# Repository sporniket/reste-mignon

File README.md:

# Sporniket's 'ReSTe mignon'

> [WARNING] Please read carefully this note before using this project. It contains important facts.

Content

1. What is **Sporniket's 'ReSTe mignon'**, and when to use it ?
2. What should you know before using **Sporniket's 'ReSTe mignon'** ?
3. How to use **Sporniket's 'ReSTe mignon'** ?
4. Known issues
5. Miscellanous

## 1. What is **Sporniket's 'ReSTe mignon'**, and when to use it ?

**Sporniket's 'ReSTe mignon'** is a _RE_-make of the computer known as 'Atari _STe_', on a B5-sized (250×175 mm) PCB. Smaller, so 'cute', hence '_mignon_'.

This is a project made with [Kicad](https://www.kicad.org/). I started this work [from the conversion of the original Atari STe schematics](https://github.com/sporniket/kicad-conversions--atari-ste-motherboard--c300780-001).

### Licence

**Sporniket's 'ReSTe mignon'** is marked with CC0 1.0 Universal. To view a copy of this license, visit http://creativecommons.org/publicdomain/zero/1.0

**Sporniket's 'ReSTe mignon'** is distributed in the hope that it will be useful, but WITHOUT ANY WARRANTY; without even the implied warranty of MERCHANTABILITY or FITNESS FOR A PARTICULAR PURPOSE.

### Releases notes

#### extension-cpu-68k-plcc68--v1.0.0-beta.1

First beta implemantion of the extension board holding the CPU in a PLCC68 package. This implements the [extension port for CPU and Blitter](README-extension-port-cpu-and-blitter.md)

#### mk0-0.1-schematic / 2022-06-08

The first complete schematics of the mark0 milestone, starting [from the conversion of the original Atari STe schematics](https://github.com/sporniket/kicad-conversions--atari-ste-motherboard--c300780-001).

  * Added DIP-64 CPU port extension
  * Removed T-filters
  * Deleted circuitry related to PAL/NTSC and modulator
  * Resolves #1 : Use 4-resistor packs wherever it is possible
  * Resolves #2 : apply the pull-up fix to data and address bus
  * Resolves #3 : Apply the DMA Pull up fix on databus
  * Resolves #4 : Apply the 1772 pull-up fix
  * Resolves #6 : Apply the reset fix
  * Resolves #5 : Apply the fix for the video ghosting
  * Resolves #7 : Assign SMD footprints to resistors pack
  * Resolves #8 : Assign 1206 hand-solder footprints to non polarized capacitors
  * Resolves #9 : Assign radial THT footprints to polarized capacitors
  * Resolves #10 : Remove the C103
  * Resolves #11 : Use the reference 'FB?' for the ferrite beads
  * Resolves #12 : Use the reference 'CP?' for polarized capacitors
  * Resolves #13 : assign 1206 hand-solder footprints to resistors
  * Resolves #14 : assign smd footprints for ferrite beads
  * Resolves #15 : assign smd footprints to the inductors
  * Resolves #16 : assign smd footprints to diodes
  * Resolves #17 : assign smd footprints to transistors
  * Resolves #18 : Apply the LMC mixer fix
  * Fixes #19 : Reinstate the external blitter for the mark 0 version
  * Resolves #20 : Replace polarized capacitors CP101 and CP536 by unpolarized ones
  * Resolves #21 : Change Q400 to Q405 from 2N3904 to MMBT3904
  * Resolves #22 : Change Q500 from LM78L82 to UA78L08 -- add bypass capacitor on input
  * Resolves #23 : Add internal ACSI port
  * Resolves #24 : Add an internal port to make easier to plug a RGB2HDMI
  * Fixes #28 : [BUG] Incomplete restoration of the blitter

## 2. What should you know before using **Sporniket's 'ReSTe mignon'** ?

**Sporniket's 'ReSTe mignon'** is made using [Kicad](https://www.kicad.org/).

The git repository use several submodules that one has to fetch in order to get the symbols, footprint and 3dmodels. One submodule requires [python3](https://www.python.org) and [GNU make](https://www.gnu.org/software/make/) to generate the libraries of symbols for integrated circuits.

> Do not use **Sporniket's 'ReSTe mignon'** if this project is not suitable for your project.

## 3. How to use **Sporniket's 'ReSTe mignon'** ?

### From sources

To get the latest available models, one must clone the git repository **and the submodules**. Then some modules needs a build step to generate its libraries.

	git clone --recurse-submodules https://github.com/sporniket/reste-mignon.git
	cd reste-mignon/kicad-symbols-generated
	make

Then, open the project in Kicad.

### From github releases

A github **schematic only** release (with `schematics` in the release tag and name) will provide a PDF of the schematics

A github **regular** release will provide :

* A standalone Kicad project (all custom libraries included and ready to use)
* A PDF of the schematics
* A PDF of the silkscreen
* If applicable, a Gerber for boardmanufacturer. Some details may have been adapted for a specific manufacturer.
* If applicable, a BOM, and pick an place files, likely for a specific manufacturer too.

## 4. Known issues
See the [project issues](https://github.com/sporniket/reste-mignon/issues) page.

## 5. Miscellanous

### Report issues
Use the [project issues](https://github.com/sporniket/reste-mignon/issues) page.

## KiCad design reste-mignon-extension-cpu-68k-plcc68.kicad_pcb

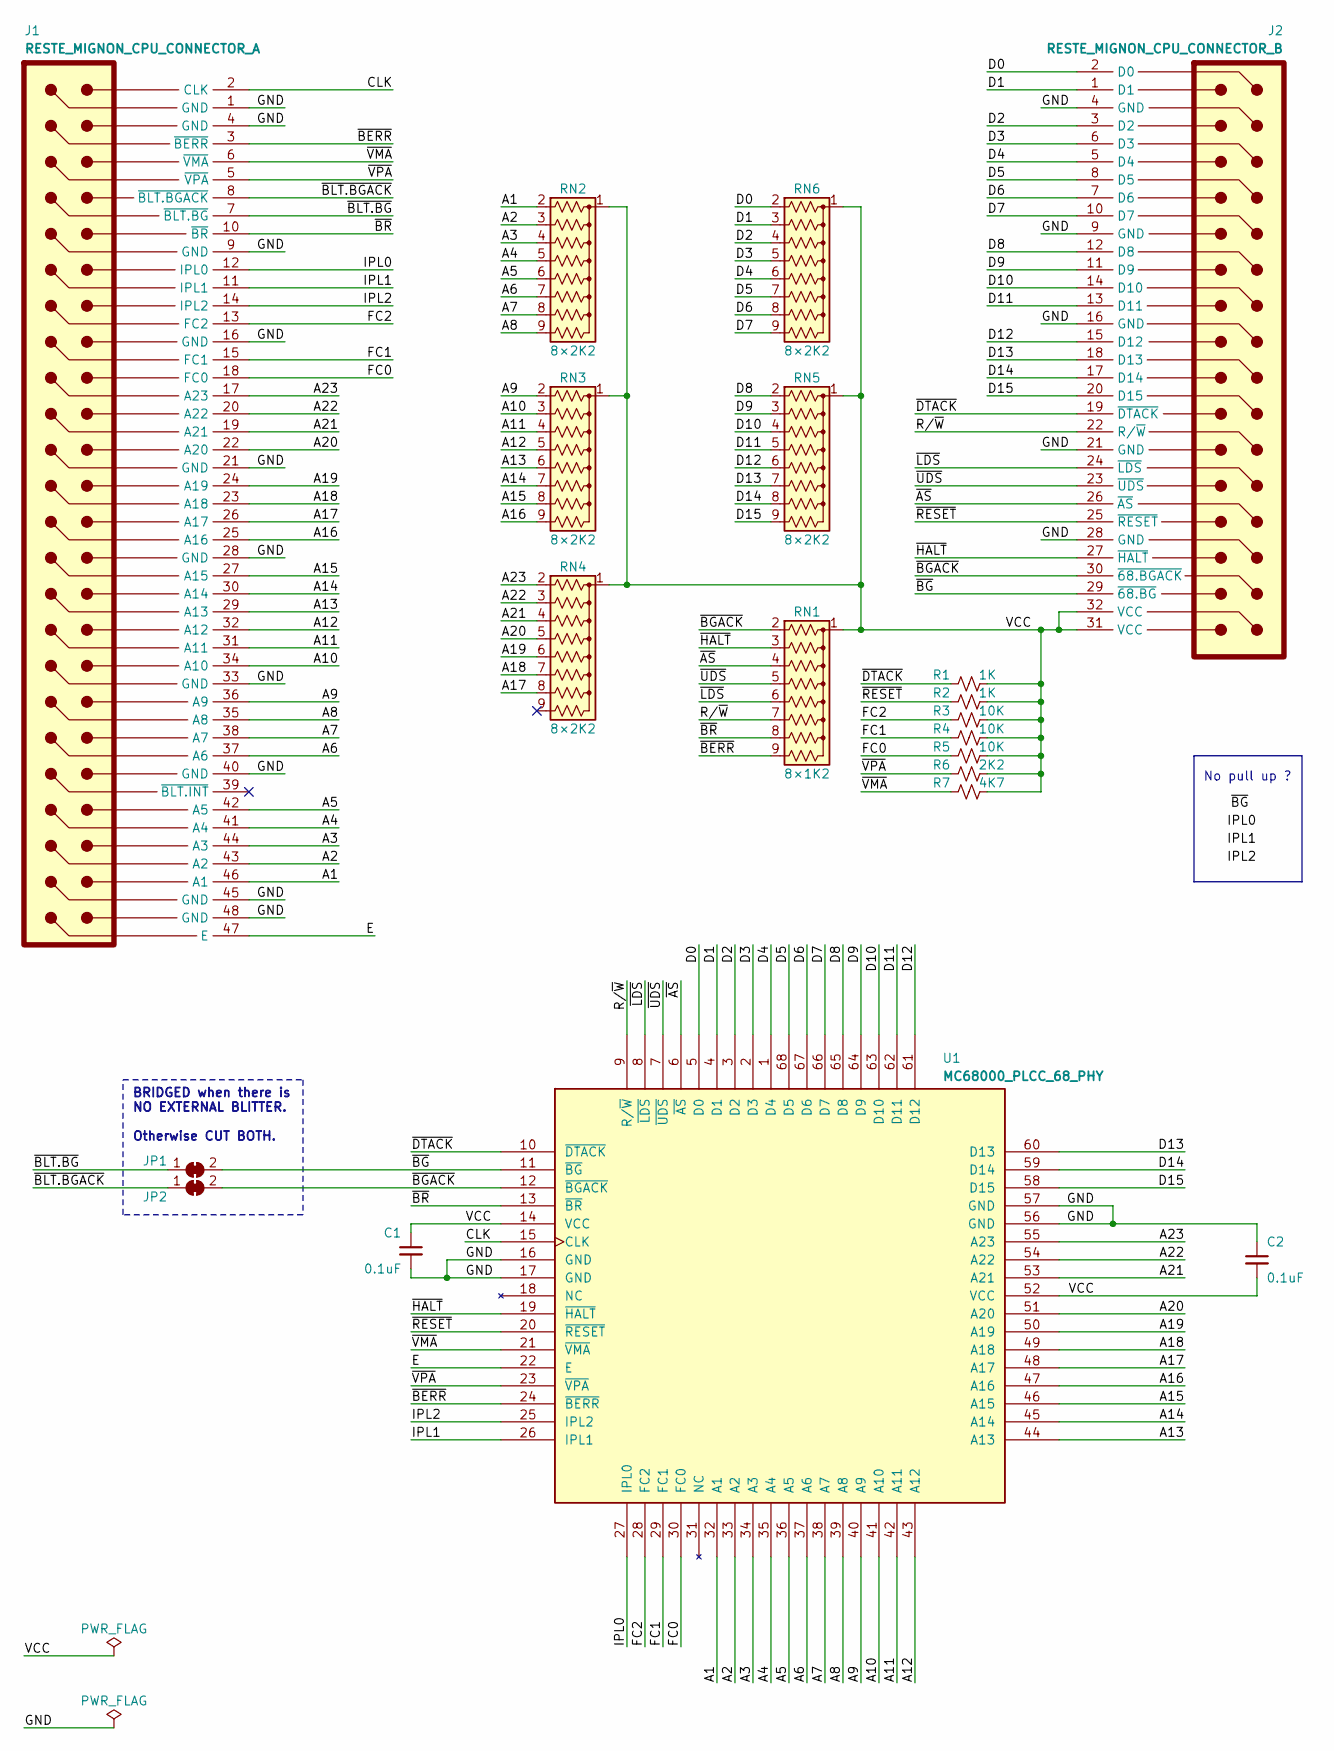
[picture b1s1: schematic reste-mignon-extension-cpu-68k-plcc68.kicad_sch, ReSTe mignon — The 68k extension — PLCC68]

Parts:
C1, C2: 0.1uF; Passive_THT_capacitor_mlcc_W2.54mm_L5.08mm
J1: RESTE_MIGNON_CPU_CONNECTOR_A; PinHeader_2x24_P2.54mm_Vertical
J2: RESTE_MIGNON_CPU_CONNECTOR_B; PinHeader_2x16_P2.54mm_Vertical
JP1, JP2: SolderJumper-2_P1.3mm_Bridged_RoundedPad1.0x1.5mm
R1, R2: 1K; Passive_THT_resistor_W2.54mm_L10.16mm
R3, R4, R5: 10K; Passive_THT_resistor_W2.54mm_L10.16mm
R6: 2K2; Passive_THT_resistor_W2.54mm_L10.16mm
R7: 4K7; Passive_THT_resistor_W2.54mm_L10.16mm
RN1: 8×1K2; R_Array_SIP9
RN2, RN3, RN4, RN5, RN6: 8×2K2; R_Array_SIP9
U1: MC68000_PLCC_68_PHY; PLCC-68_THT-Socket

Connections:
/A1: J1.46 (A1), RN2.2 (R1), U1.32 (A1)
/A2: J1.43 (A2), RN2.3 (R2), U1.33 (A2)
/A3: J1.44 (A3), RN2.4 (R3), U1.34 (A3)
/A4: J1.41 (A4), RN2.5 (R4), U1.35 (A4)
/A5: J1.42 (A5), RN2.6 (R5), U1.36 (A5)
/A6: J1.37 (A6), RN2.7 (R6), U1.37 (A6)
/A7: J1.38 (A7), RN2.8 (R7), U1.38 (A7)
/A8: J1.35 (A8), RN2.9 (R8), U1.39 (A8)
/A9: J1.36 (A9), RN3.2 (R1), U1.40 (A9)
/A10: J1.34 (A10), RN3.3 (R2), U1.41 (A10)
/A11: J1.31 (A11), RN3.4 (R3), U1.42 (A11)
/A12: J1.32 (A12), RN3.5 (R4), U1.43 (A12)
/A13: J1.29 (A13), RN3.6 (R5), U1.44 (A13)
/A14: J1.30 (A14), RN3.7 (R6), U1.45 (A14)
/A15: J1.27 (A15), RN3.8 (R7), U1.46 (A15)
/A16: J1.25 (A16), RN3.9 (R8), U1.47 (A16)
/A17: J1.26 (A17), RN4.8 (R7), U1.48 (A17)
/A18: J1.23 (A18), RN4.7 (R6), U1.49 (A18)
/A19: J1.24 (A19), RN4.6 (R5), U1.50 (A19)
/A20: J1.22 (A20), RN4.5 (R4), U1.51 (A20)
/A21: J1.19 (A21), RN4.4 (R3), U1.53 (A21)
/A22: J1.20 (A22), RN4.3 (R2), U1.54 (A22)
/A23: J1.17 (A23), RN4.2 (R1), U1.55 (A23)
/CLK: J1.2 (CLK), U1.15 (CLK)
/D0: J2.2 (D0), RN6.2 (R1), U1.5 (D0)
/D1: J2.1 (D1), RN6.3 (R2), U1.4 (D1)
/D2: J2.3 (D2), RN6.4 (R3), U1.3 (D2)
/D3: J2.6 (D3), RN6.5 (R4), U1.2 (D3)
/D4: J2.5 (D4), RN6.6 (R5), U1.1 (D4)
/D5: J2.8 (D5), RN6.7 (R6), U1.68 (D5)
/D6: J2.7 (D6), RN6.8 (R7), U1.67 (D6)
/D7: J2.10 (D7), RN6.9 (R8), U1.66 (D7)
/D8: J2.12 (D8), RN5.2 (R1), U1.65 (D8)
/D9: J2.11 (D9), RN5.3 (R2), U1.64 (D9)
/D10: J2.14 (D10), RN5.4 (R3), U1.63 (D10)
/D11: J2.13 (D11), RN5.5 (R4), U1.62 (D11)
/D12: J2.15 (D12), RN5.6 (R5), U1.61 (D12)
/D13: J2.18 (D13), RN5.7 (R6), U1.60 (D13)
/D14: J2.17 (D14), RN5.8 (R7), U1.59 (D14)
/D15: J2.20 (D15), RN5.9 (R8), U1.58 (D15)
/E: J1.47 (E), U1.22 (E)
/FC0: J1.18 (FC0), R5.1, U1.30 (FC0)
/FC1: J1.15 (FC1), R4.1, U1.29 (FC1)
/FC2: J1.13 (FC2), R3.1, U1.28 (FC2)
/GND: C1.2, C2.1, J1.1 (GND), J1.4 (GND), J1.9 (GND), J1.16 (GND), J1.21 (GND), J1.28 (GND), J1.33 (GND), J1.40 (GND), J1.45 (GND), J1.48 (GND), J2.4 (GND), J2.9 (GND), J2.16 (GND), J2.21 (GND), J2.28 (GND), U1.16 (GND), U1.17 (GND), U1.56 (GND), U1.57 (GND)
/IPL0: J1.12 (IPL0), U1.27 (IPL0)
/IPL1: J1.11 (IPL1), U1.26 (IPL1)
/IPL2: J1.14 (IPL2), U1.25 (IPL2)
/R/~W: J2.22 (R/~W), RN1.7 (R6), U1.9 (R/~W)
/VCC: C1.1, C2.2, J2.31 (VCC), J2.32 (VCC), R1.2, R2.2, R3.2, R4.2, R5.2, R6.2, R7.2, RN1.1 (common), RN2.1 (common), RN3.1 (common), RN4.1 (common), RN5.1 (common), RN6.1 (common), U1.14 (VCC), U1.52 (VCC)
/~AS: J2.26 (~AS), RN1.4 (R3), U1.6 (~AS)
/~BERR: J1.3 (~BERR), RN1.9 (R8), U1.24 (~BERR)
/~BGACK: J2.30 (~68.BGACK), JP2.2 (B), RN1.2 (R1), U1.12 (~BGACK)
/~BG: J2.29 (~68.BG), JP1.2 (B), U1.11 (~BG)
/~BLT.BGACK: J1.8 (~BLT.BGACK), JP2.1 (A)
/~BLT.BG: J1.7 (~BLT.BG), JP1.1 (A)
/~BR: J1.10 (~BR), RN1.8 (R7), U1.13 (~BR)
/~DTACK: J2.19 (~DTACK), R1.1, U1.10 (~DTACK)
/~HALT: J2.27 (~HALT), RN1.3 (R2), U1.19 (~HALT)
/~LDS: J2.24 (~LDS), RN1.6 (R5), U1.8 (~LDS)
/~RESET: J2.25 (~RESET), R2.1, U1.20 (~RESET)
/~UDS: J2.23 (~UDS), RN1.5 (R4), U1.7 (~UDS)
/~VMA: J1.6 (~VMA), R7.1, U1.21 (~VMA)
/~VPA: J1.5 (~VPA), R6.1, U1.23 (~VPA)

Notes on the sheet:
No pull up ?
BRIDGED when there is NO EXTERNAL BLITTER. Otherwise CUT BOTH.

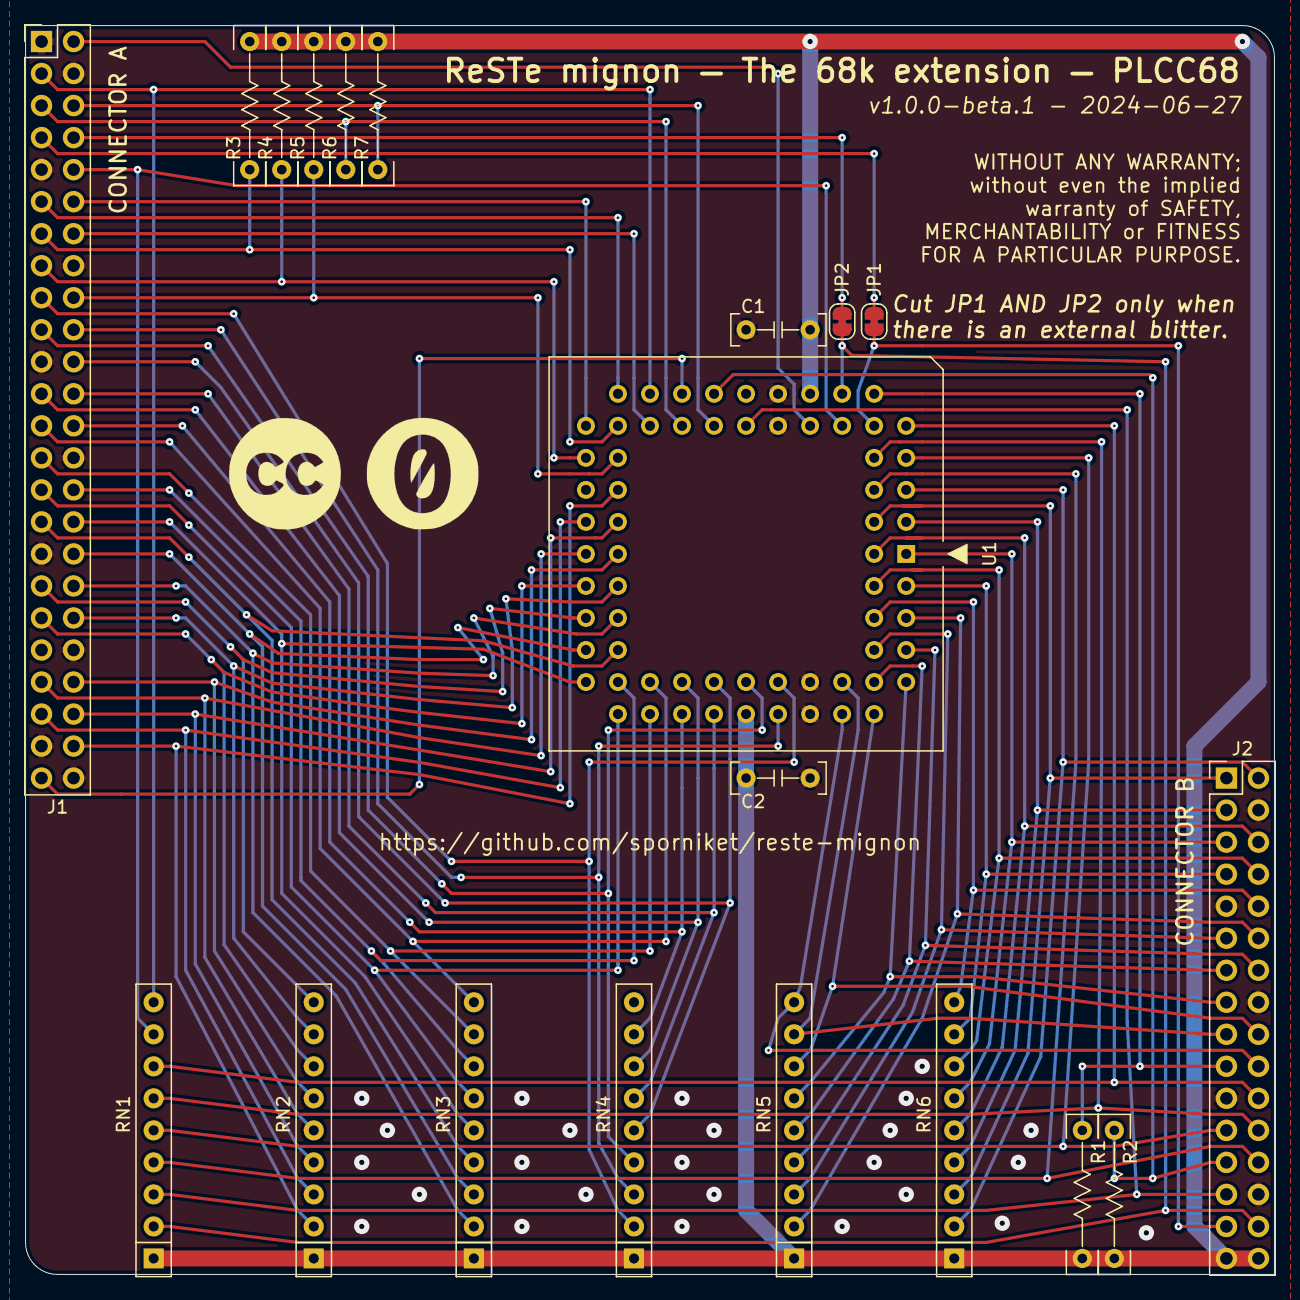
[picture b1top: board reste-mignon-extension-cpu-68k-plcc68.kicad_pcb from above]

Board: 4 copper layers, 99.1 x 99.1 mm, 20 parts (0 on the bottom side), 64 nets.

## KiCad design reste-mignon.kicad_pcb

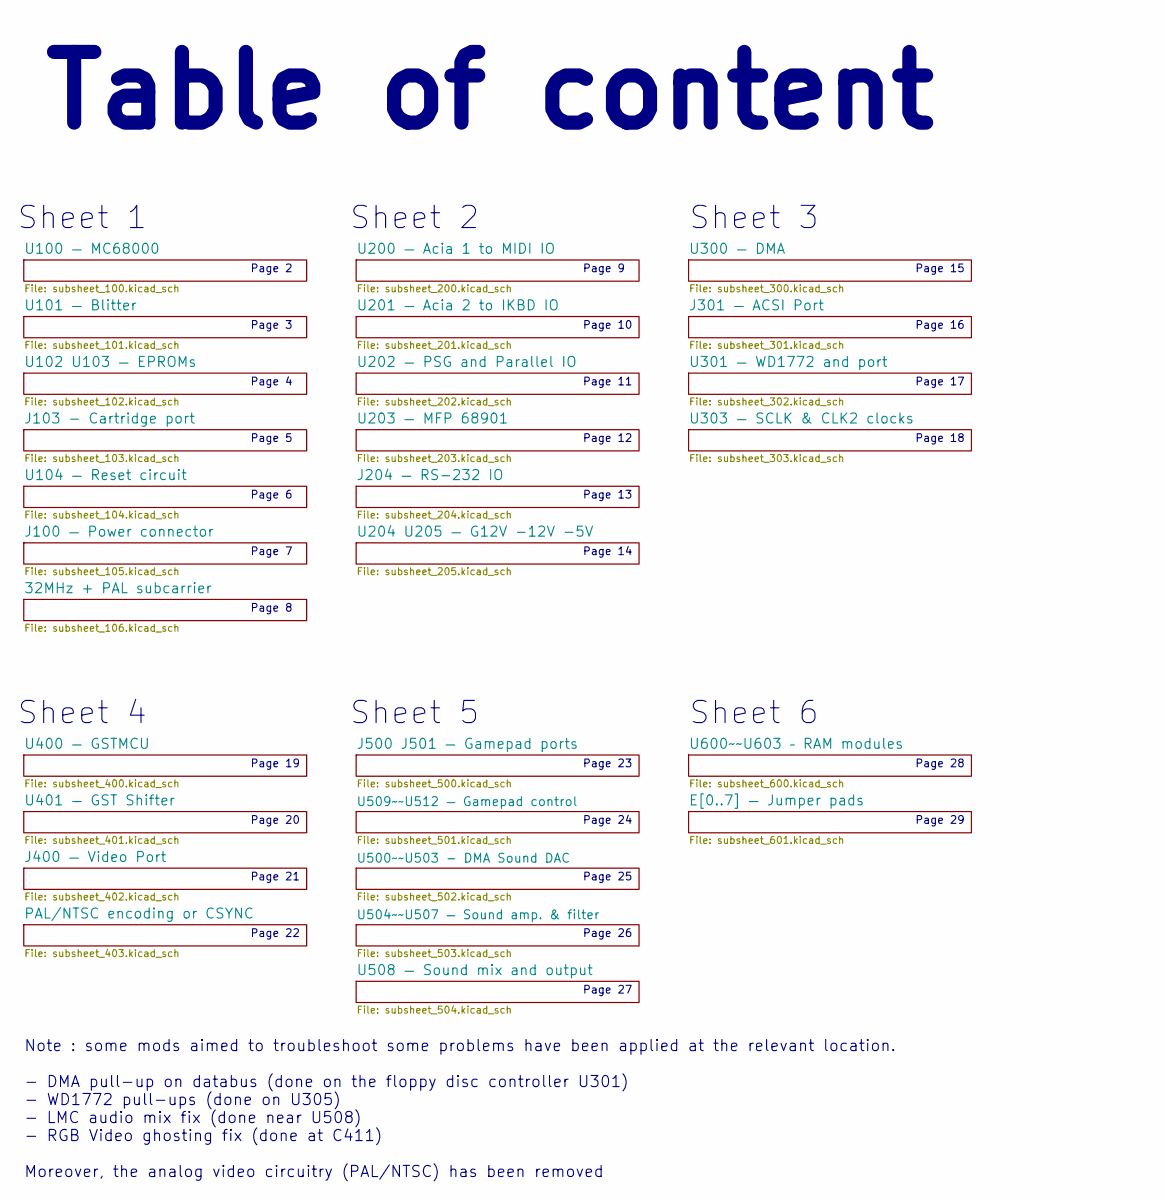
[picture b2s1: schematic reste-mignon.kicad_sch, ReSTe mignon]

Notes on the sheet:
Note : some mods aimed to troubleshoot some problems have been applied at the relevant location. - DMA pull-up on databus (done on the floppy disc controller U301) - WD1772 pull-ups (done on U305) - LMC audio mix fix (done near U508) - RGB Video ghosting fix (done at C411) Moreover, the analog vide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
Page 15
Page 14
Page 24
Page 25
Sheet 3
Page 10
Page 23
Page 9
Page 4
Page 13
Page 27
Page 20
Page 28
Page 6
Page 16
Page 2
Sheet 1
Sheet 4
Page 29
Page 11
Sheet 2
Page 26
Page 22
Page 17
Page 7
Sheet 5
Page 21
Page 12
Page 19
Page 18
Page 3
Table of content
Sheet 6
Page 8
Page 5

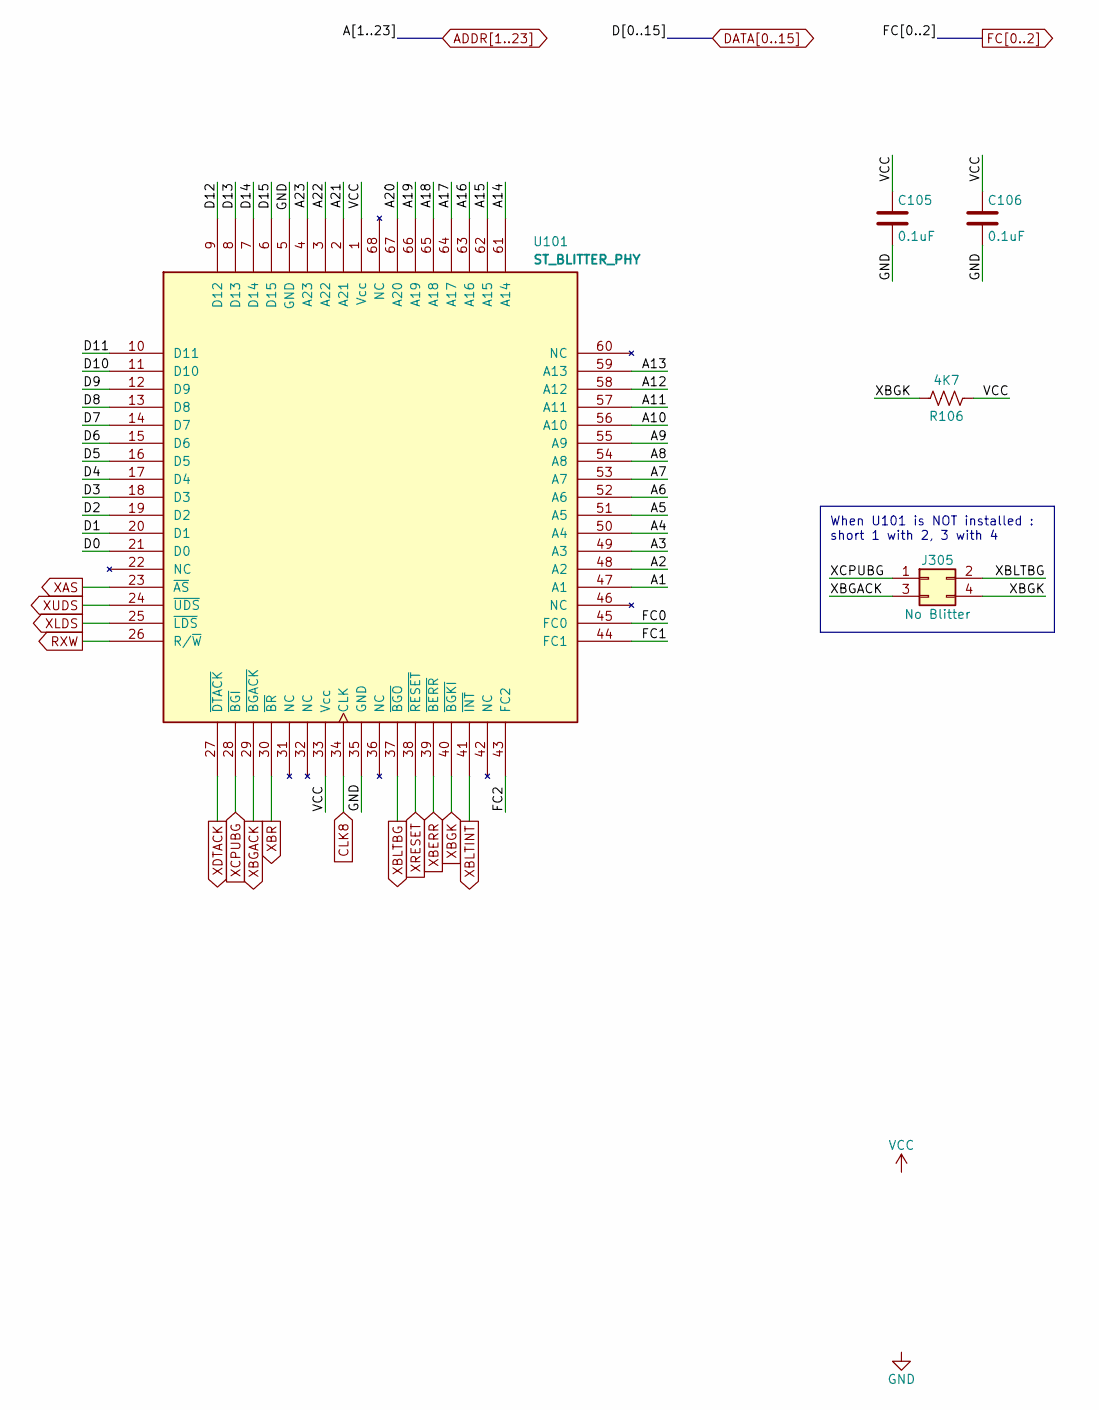
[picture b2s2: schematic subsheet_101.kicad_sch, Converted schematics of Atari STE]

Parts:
C105, C106: 0.1uF; C_1206_3216Metric_Pad1.33x1.80mm_HandSolder
J305: No Blitter; PinHeader_2x02_P2.54mm_Vertical
R106: 4K7; R_1206_3216Metric_Pad1.30x1.75mm_HandSolder
U101: ST_BLITTER_PHY; PLCC-68_THT-Socket

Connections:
ADDR1: U101.47 (A1); also elsewhere on the board
ADDR2: U101.48 (A2); also elsewhere on the board
ADDR3: U101.49 (A3); also elsewhere on the board
ADDR4: U101.50 (A4); also elsewhere on the board
ADDR5: U101.51 (A5); also elsewhere on the board
ADDR6: U101.52 (A6); also elsewhere on the board
ADDR7: U101.53 (A7); also elsewhere on the board
ADDR8: U101.54 (A8); also elsewhere on the board
ADDR9: U101.55 (A9); also elsewhere on the board
ADDR10: U101.56 (A10); also elsewhere on the board
ADDR11: U101.57 (A11); also elsewhere on the board
ADDR12: U101.58 (A12); also elsewhere on the board
ADDR13: U101.59 (A13); also elsewhere on the board
ADDR14: U101.61 (A14); also elsewhere on the board
ADDR15: U101.62 (A15); also elsewhere on the board
ADDR16: U101.63 (A16); also elsewhere on the board
ADDR17: U101.64 (A17); also elsewhere on the board
ADDR18: U101.65 (A18); also elsewhere on the board
ADDR19: U101.66 (A19); also elsewhere on the board
ADDR20: U101.67 (A20); also elsewhere on the board
ADDR21: U101.2 (A21); also elsewhere on the board
ADDR22: U101.3 (A22); also elsewhere on the board
ADDR23: U101.4 (A23); also elsewhere on the board
CLK8: U101.34 (CLK); also elsewhere on the board
DATA0: U101.21 (D0); also elsewhere on the board
DATA1: U101.20 (D1); also elsewhere on the board
DATA2: U101.19 (D2); also elsewhere on the board
DATA3: U101.18 (D3); also elsewhere on the board
DATA4: U101.17 (D4); also elsewhere on the board
DATA5: U101.16 (D5); also elsewhere on the board
DATA6: U101.15 (D6); also elsewhere on the board
DATA7: U101.14 (D7); also elsewhere on the board
DATA8: U101.13 (D8); also elsewhere on the board
DATA9: U101.12 (D9); also elsewhere on the board
DATA10: U101.11 (D10); also elsewhere on the board
DATA11: U101.10 (D11); also elsewhere on the board
DATA12: U101.9 (D12); also elsewhere on the board
DATA13: U101.8 (D13); also elsewhere on the board
DATA14: U101.7 (D14); also elsewhere on the board
DATA15: U101.6 (D15); also elsewhere on the board
FC0: U101.45 (FC0); also elsewhere on the board
FC1: U101.44 (FC1); also elsewhere on the board
FC2: U101.43 (FC2); also elsewhere on the board
GND: C105.2, C106.2, U101.5 (GND), U101.35 (GND); also elsewhere on the board
RXW: U101.26 (R/~W); also elsewhere on the board
VCC: C105.1, C106.1, R106.1, U101.1 (Vcc), U101.33 (Vcc); also elsewhere on the board
XAS: U101.23 (~AS); also elsewhere on the board
XBERR: U101.39 (~BERR); also elsewhere on the board
XBGACK: J305.3, U101.29 (~BGACK); also elsewhere on the board
XBGK: J305.4, R106.2, U101.40 (~BGKI); also elsewhere on the board
XBLTBG: J305.2, U101.37 (~BGO); also elsewhere on the board
XBLTINT: U101.41 (~INT); also elsewhere on the board
XBR: U101.30 (~BR); also elsewhere on the board
XCPUBG: J305.1, U101.28 (~BGI); also elsewhere on the board
XDTACK: U101.27 (~DTACK); also elsewhere on the board
XLDS: U101.25 (~LDS); also elsewhere on the board
XRESET: U101.38 (~RESET); also elsewhere on the board
XUDS: U101.24 (~UDS); also elsewhere on the board

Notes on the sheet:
When U101 is NOT installed : short 1 with 2, 3 with 4

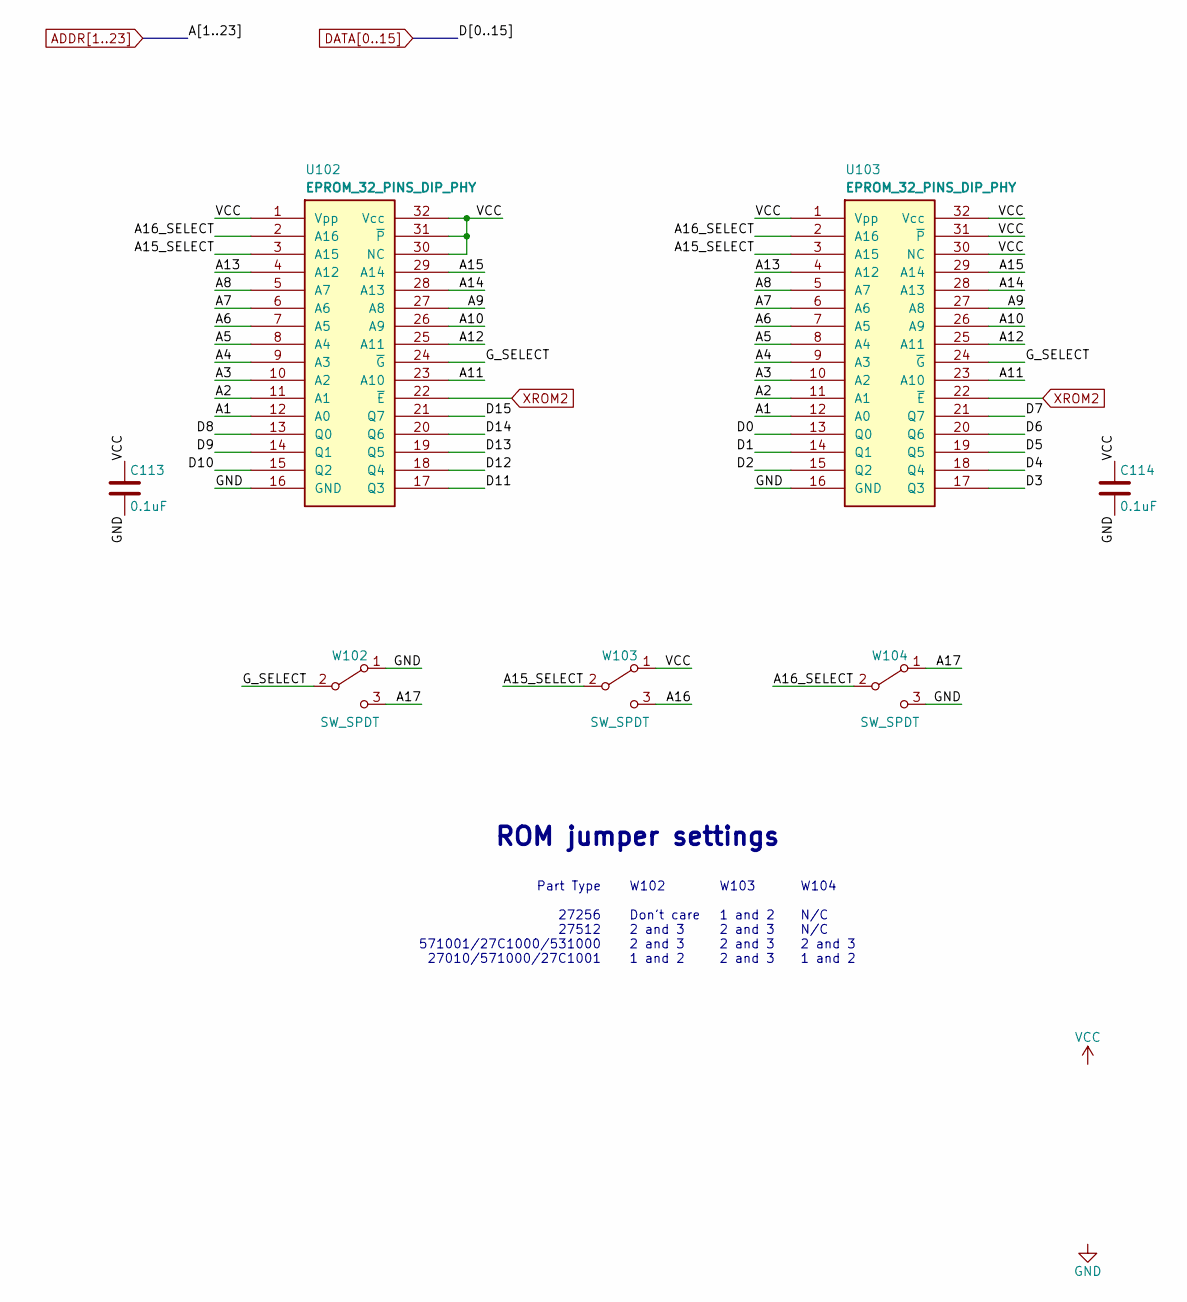
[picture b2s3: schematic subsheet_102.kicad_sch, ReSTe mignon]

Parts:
C113, C114: 0.1uF; C_1206_3216Metric_Pad1.33x1.80mm_HandSolder
U102, U103: EPROM_32_PINS_DIP_PHY; DIP-32_W15.24mm_LongPads
W102, W103, W104: SW_SPDT; PinHeader_1x03_P2.54mm_Vertical

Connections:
/U102 U103 — EPROMs/A15_SELECT: U102.3 (A15), U103.3 (A15), W103.2 (B)
/U102 U103 — EPROMs/A16_SELECT: U102.2 (A16), U103.2 (A16), W104.2 (B)
/U102 U103 — EPROMs/G_SELECT: U102.24 (~G), U103.24 (~G), W102.2 (B)
ADDR1: U102.12 (A0), U103.12 (A0); also elsewhere on the board
ADDR2: U102.11 (A1), U103.11 (A1); also elsewhere on the board
ADDR3: U102.10 (A2), U103.10 (A2); also elsewhere on the board
ADDR4: U102.9 (A3), U103.9 (A3); also elsewhere on the board
ADDR5: U102.8 (A4), U103.8 (A4); also elsewhere on the board
ADDR6: U102.7 (A5), U103.7 (A5); also elsewhere on the board
ADDR7: U102.6 (A6), U103.6 (A6); also elsewhere on the board
ADDR8: U102.5 (A7), U103.5 (A7); also elsewhere on the board
ADDR9: U102.27 (A8), U103.27 (A8); also elsewhere on the board
ADDR10: U102.26 (A9), U103.26 (A9); also elsewhere on the board
ADDR11: U102.23 (A10), U103.23 (A10); also elsewhere on the board
ADDR12: U102.25 (A11), U103.25 (A11); also elsewhere on the board
ADDR13: U102.4 (A12), U103.4 (A12); also elsewhere on the board
ADDR14: U102.28 (A13), U103.28 (A13); also elsewhere on the board
ADDR15: U102.29 (A14), U103.29 (A14); also elsewhere on the board
ADDR16: W103.3 (C); also elsewhere on the board
ADDR17: W102.3 (C), W104.1 (A); also elsewhere on the board
DATA0: U103.13 (Q0); also elsewhere on the board
DATA1: U103.14 (Q1); also elsewhere on the board
DATA2: U103.15 (Q2); also elsewhere on the board
DATA3: U103.17 (Q3); also elsewhere on the board
DATA4: U103.18 (Q4); also elsewhere on the board
DATA5: U103.19 (Q5); also elsewhere on the board
DATA6: U103.20 (Q6); also elsewhere on the board
DATA7: U103.21 (Q7); also elsewhere on the board
DATA8: U102.13 (Q0); also elsewhere on the board
DATA9: U102.14 (Q1); also elsewhere on the board
DATA10: U102.15 (Q2); also elsewhere on the board
DATA11: U102.17 (Q3); also elsewhere on the board
DATA12: U102.18 (Q4); also elsewhere on the board
DATA13: U102.19 (Q5); also elsewhere on the board
DATA14: U102.20 (Q6); also elsewhere on the board
DATA15: U102.21 (Q7); also elsewhere on the board
GND: C113.2, C114.2, U102.16 (GND), U103.16 (GND), W102.1 (A), W104.3 (C); also elsewhere on the board
VCC: C113.1, C114.1, U102.1 (Vpp), U102.30 (NC), U102.31 (~P), U102.32 (Vcc), U103.1 (Vpp), U103.30 (NC), U103.31 (~P), U103.32 (Vcc), W103.1 (A); also elsewhere on the board
XROM2: U102.22 (~E), U103.22 (~E); also elsewhere on the board

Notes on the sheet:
ROM jumper settings
W103 1 and 2 2 and 3 2 and 3 2 and 3
Part Type 27256 27512 571001/27C1000/531000 27010/571000/27C1001
W104 N/C N/C 2 and 3 1 and 2
W102 Don't care 2 and 3 2 and 3 1 and 2

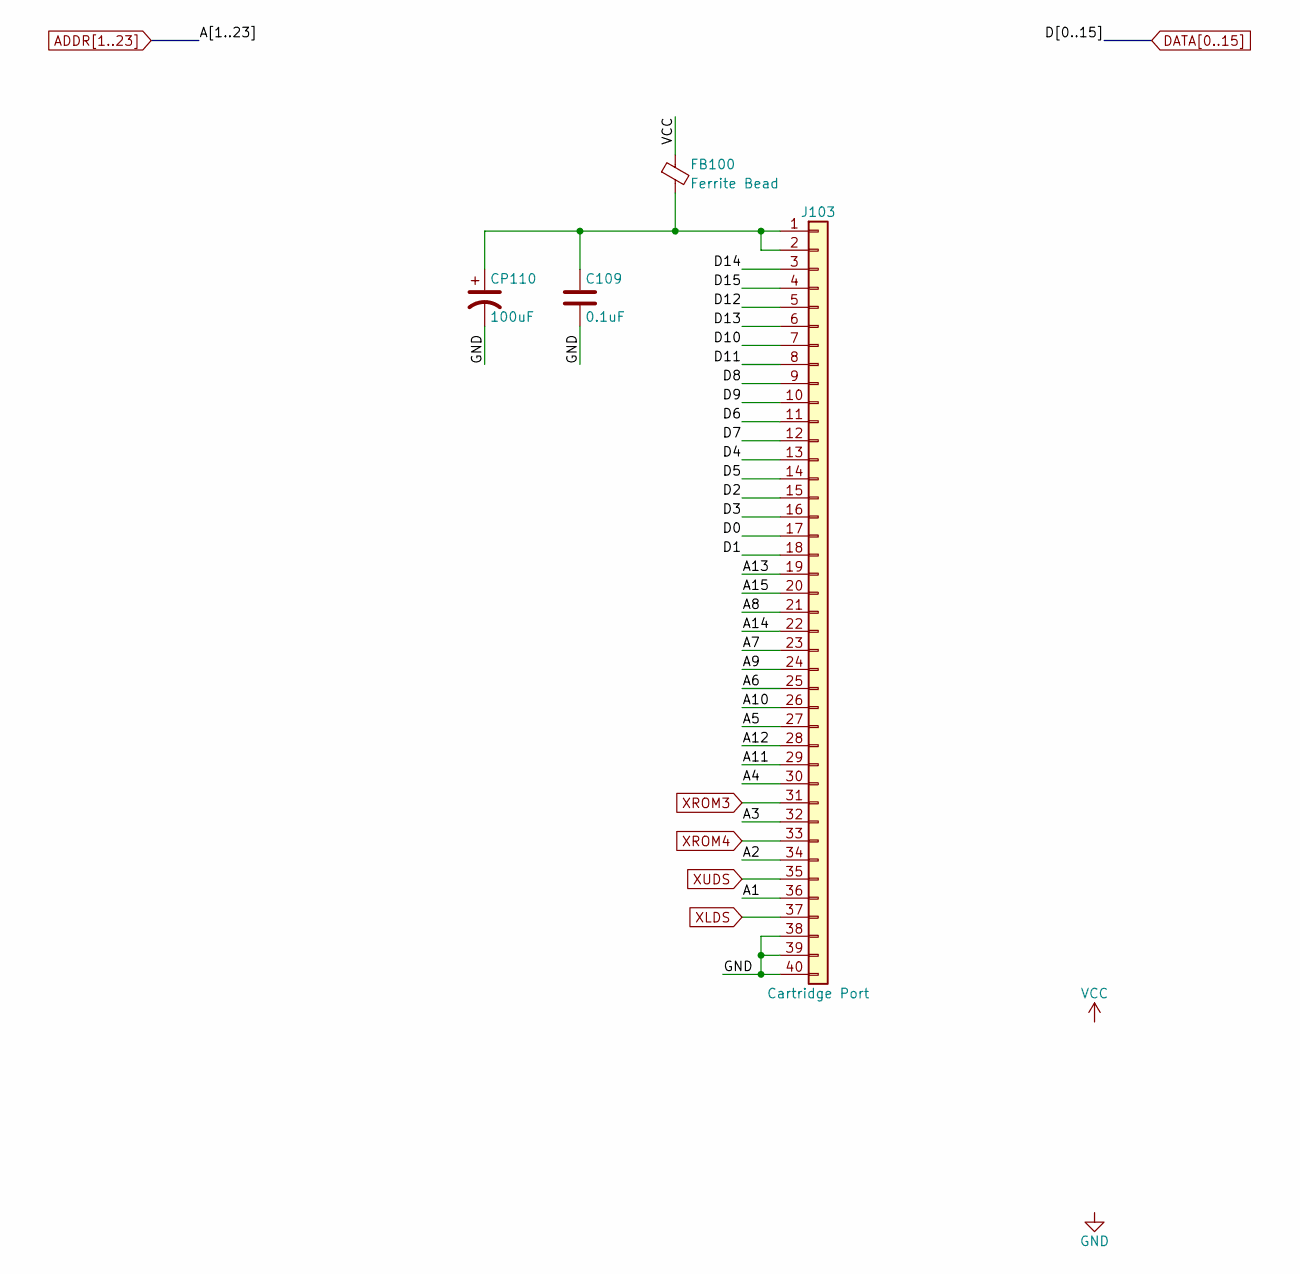
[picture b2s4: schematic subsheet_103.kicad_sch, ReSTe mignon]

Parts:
C109: 0.1uF; C_1206_3216Metric_Pad1.33x1.80mm_HandSolder
CP110: 100uF; C_Radial_D8.0mm_H11.5mm_P3.50mm
FB100: Ferrite Bead; L_1206_3216Metric_Pad1.22x1.90mm_HandSolder
J103: Cartridge Port; socket-edge-pcb_40p_P2.01mm

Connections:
ADDR1: J103.36; also elsewhere on the board
ADDR2: J103.34; also elsewhere on the board
ADDR3: J103.32; also elsewhere on the board
ADDR4: J103.30; also elsewhere on the board
ADDR5: J103.27; also elsewhere on the board
ADDR6: J103.25; also elsewhere on the board
ADDR7: J103.23; also elsewhere on the board
ADDR8: J103.21; also elsewhere on the board
ADDR9: J103.24; also elsewhere on the board
ADDR10: J103.26; also elsewhere on the board
ADDR11: J103.29; also elsewhere on the board
ADDR12: J103.28; also elsewhere on the board
ADDR13: J103.19; also elsewhere on the board
ADDR14: J103.22; also elsewhere on the board
ADDR15: J103.20; also elsewhere on the board
DATA0: J103.17; also elsewhere on the board
DATA1: J103.18; also elsewhere on the board
DATA2: J103.15; also elsewhere on the board
DATA3: J103.16; also elsewhere on the board
DATA4: J103.13; also elsewhere on the board
DATA5: J103.14; also elsewhere on the board
DATA6: J103.11; also elsewhere on the board
DATA7: J103.12; also elsewhere on the board
DATA8: J103.9; also elsewhere on the board
DATA9: J103.10; also elsewhere on the board
DATA10: J103.7; also elsewhere on the board
DATA11: J103.8; also elsewhere on the board
DATA12: J103.5; also elsewhere on the board
DATA13: J103.6; also elsewhere on the board
DATA14: J103.3; also elsewhere on the board
DATA15: J103.4; also elsewhere on the board
GND: C109.2, CP110.2, J103.38, J103.39, J103.40; also elsewhere on the board
unnamed: C109.1, CP110.1, FB100.2, J103.1, J103.2
VCC: FB100.1; also elsewhere on the board
XLDS: J103.37; also elsewhere on the board
XROM3: J103.31; also elsewhere on the board
XROM4: J103.33; also elsewhere on the board
XUDS: J103.35; also elsewhere on the board

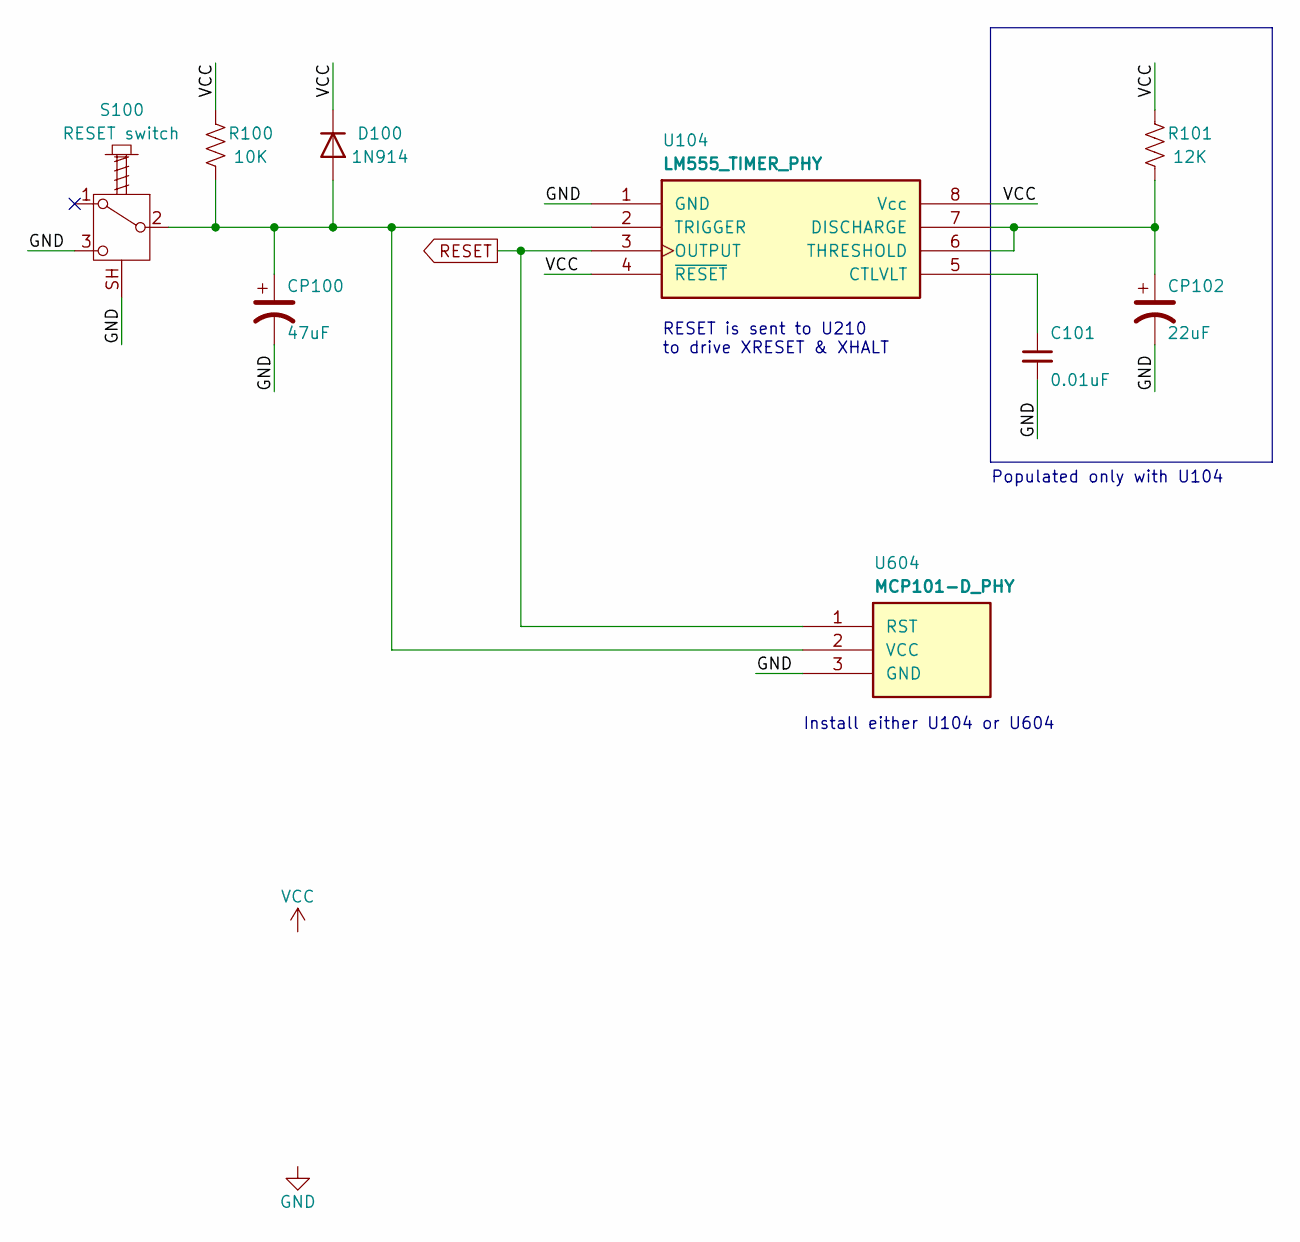
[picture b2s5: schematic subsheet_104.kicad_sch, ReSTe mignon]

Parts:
C101: 0.01uF; C_1206_3216Metric_Pad1.33x1.80mm_HandSolder
CP100: 47uF; C_Radial_D6.3mm_H11.0mm_P2.50mm
CP102: 22uF; C_Radial_D5.0mm_H11.0mm_P2.00mm
D100: 1N914; D_SOD-123F
R100: 10K; R_1206_3216Metric_Pad1.30x1.75mm_HandSolder
R101: 12K; R_1206_3216Metric_Pad1.30x1.75mm_HandSolder
S100: RESET switch; switch-spdt-momentary-action_Reset_pushbutton
U104: LM555_TIMER_PHY; DIP-8_W7.62mm_LongPads
U604: MCP101-D_PHY; TO-92L_Inline

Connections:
GND: C101.2, CP100.2, CP102.2, S100.3 (C), S100.SH (Shield), U104.1 (GND), U604.3 (GND); also elsewhere on the board
unnamed: CP100.1, D100.2 (A), R100.2, S100.2 (B), U104.2 (TRIGGER), U604.2 (VCC)
unnamed: C101.1, U104.5 (CTLVLT)
unnamed: CP102.1, R101.2, U104.6 (THRESHOLD), U104.7 (DISCHARGE)
RESET: U104.3 (OUTPUT), U604.1 (RST); also elsewhere on the board
VCC: D100.1 (K), R100.1, R101.1, U104.4 (~RESET), U104.8 (Vcc); also elsewhere on the board

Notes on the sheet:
Install either U104 or U604
Populated only with U104
RESET is sent to U210 to drive XRESET & XHALT
